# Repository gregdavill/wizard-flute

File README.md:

# Wizard Flute #

     ~ Current Status: Prototype boards ordered ~
     
     Note: This design was performed in KiCad nightly , you will need a Nightly build to open and edit these source files.

## What is it?

ESP32-S2 + LED Display

A Compact 4 digit 7-segment clock display with an ESP32-S2 control board.

It is powered off a USB-C connection on the side of the unit, and features 1 button.

This design will become a desk clock that sets it's time from your local WiFi using NTP.

## Licence
 * Hardware in this repository is licensed under CERN-OHL-P

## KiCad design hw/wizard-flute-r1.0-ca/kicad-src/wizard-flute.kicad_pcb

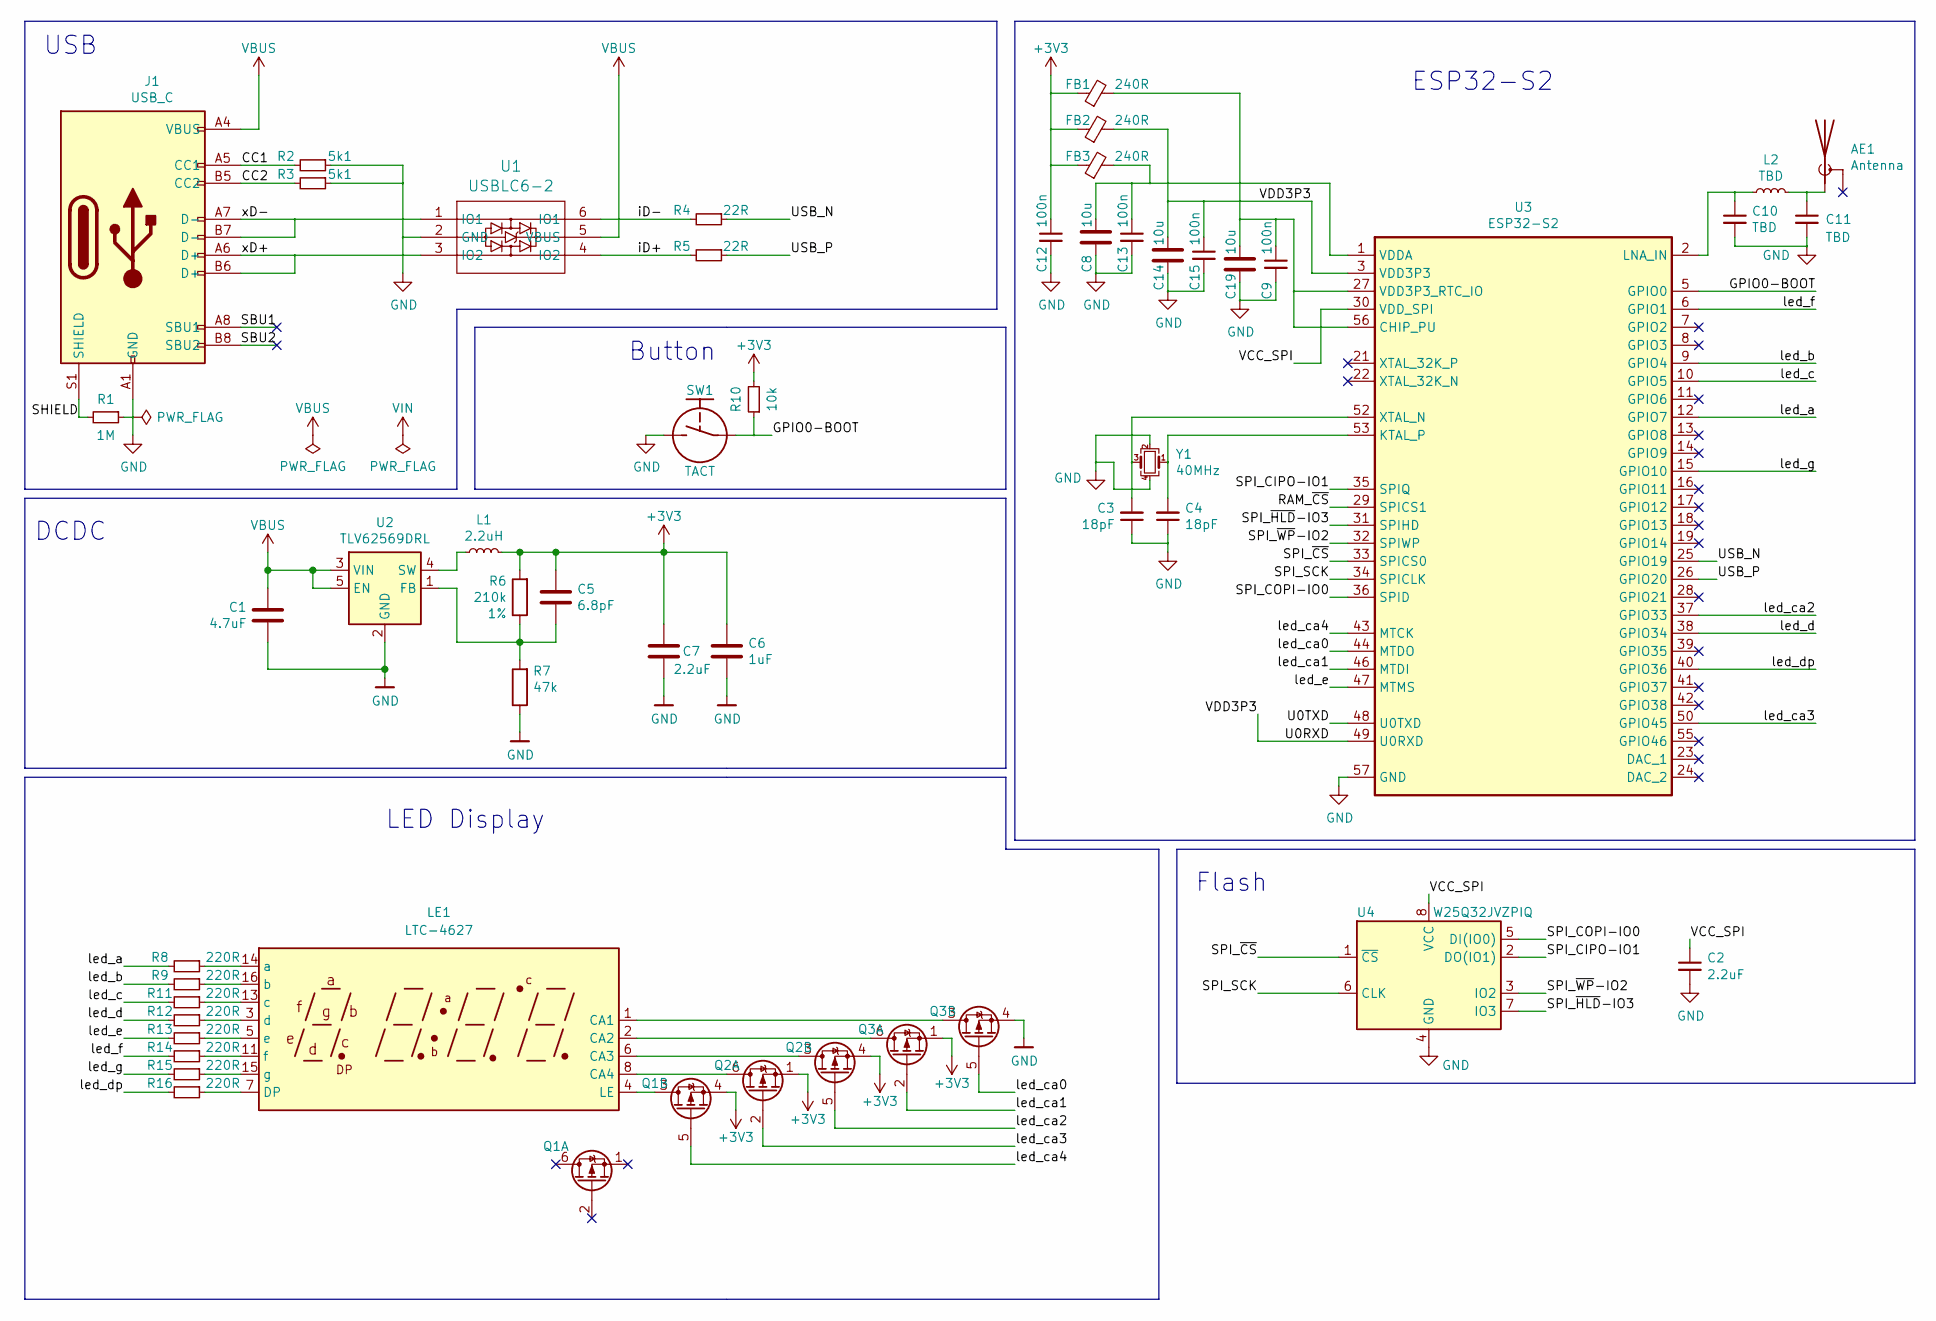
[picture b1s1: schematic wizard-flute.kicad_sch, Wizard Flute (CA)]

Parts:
AE1: Antenna; Ant_3216
C1: 4.7uF; C_0402_1005Metric
C2, C7: 2.2uF; C_0402_1005Metric
C3, C4: 18pF; C_0402_1005Metric
C5: 6.8pF; C_0402_1005Metric
C6: 1uF; C_0402_1005Metric
C8, C14, C19: 10u; C_0603_1608Metric
C9, C12, C13, C15: 100n; C_0402_1005Metric
C10, C11: TBD; C_0402_1005Metric
FB1, FB2, FB3: 240R; L_0402_1005Metric
J1: USB_C; USB_C_Receptacle_HRO_TYPE-C-31-M-12
L1: 2.2uH; L_0805_2012Metric
L2: TBD; L_0402_1005Metric
LE1: LTC-4627; kem-3942-ay
Q1, Q2, Q3: NTZD3152P; SOT-666
R1: 1M; R_0402_1005Metric
R2, R3: 5k1; R_0402_1005Metric
R4, R5: 22R; R_0402_1005Metric
R6: 210k; R_0402_1005Metric
R7: 47k; R_0402_1005Metric
R8, R9, R11, R12, R13, R14, R15, R16: 220R; R_0402_1005Metric
R10: 10k; R_0402_1005Metric
SW1: TACT; SW_SPST_3x4x2.5
U1: USBLC6-2; SOT-666
U2: TLV62569DRL; SOT-666
U3: ESP32-S2; QFN-56-1EP_7x7mm_P0.4mm_EP5.6x5.6mm
U4: W25Q32JVZPIQ; WSON-8-1EP_6x5mm_P1.27mm_EP3.4x4mm
Y1: 40MHz; Crystal_SMD_4Pin_2.0x1.6mm

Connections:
+3V3: C5.1, C6.1, C7.1, C12.1, FB1.1, FB2.1, FB3.1, L1.2, Q1.4 (S), Q2.1 (S), Q2.4 (S), Q3.1 (S), R6.2, R10.2
/CC1: J1.A5 (CC1), R2.2
/CC2: J1.B5 (CC2), R3.2
/GPIO0-BOOT: R10.1, SW1.1, U3.5 (GPIO0)
/RAM_~CS: U3.29 (SPICS1)
/SBU1: J1.A8 (SBU1)
/SBU2: J1.B8 (SBU2)
/SHIELD: J1.S1 (SHIELD), R1.2
/SPI_CIPO-IO1: U3.35 (SPIQ), U4.2 (DO(IO1))
/SPI_COPI-IO0: U3.36 (SPID), U4.5 (DI(IO0))
/SPI_SCK: U3.34 (SPICLK), U4.6 (CLK)
/SPI_~CS: U3.33 (SPICS0), U4.1 (~CS)
/SPI_~HLD~-IO3: U3.31 (SPIHD), U4.7 (IO3)
/SPI_~WP~-IO2: U3.32 (SPIWP), U4.3 (IO2)
/U0RXD: C14.1, C15.1, FB2.2, U3.3 (VDD3P3), U3.4 (VDD3P3), U3.49 (U0RXD)
/U0TXD: U3.48 (U0TXD)
/USB_N: R4.1, U3.25 (GPIO19)
/USB_P: R5.1, U3.26 (GPIO20)
/VCC_SPI: C2.1, U3.30 (VDD_SPI), U4.8 (VCC)
/iD+: R5.2, U1.4 (IO2)
/iD-: R4.2, U1.6 (IO1)
/led_a: R8.2, U3.12 (GPIO7)
/led_b: R9.2, U3.9 (GPIO4)
/led_c: R11.2, U3.10 (GPIO5)
/led_ca0: Q3.5 (G), U3.44 (MTDO)
/led_ca1: Q3.2 (G), U3.46 (MTDI)
/led_ca2: Q2.5 (G), U3.37 (GPIO33)
/led_ca3: Q2.2 (G), U3.50 (GPIO45)
/led_ca4: Q1.5 (G), U3.43 (MTCK)
/led_d: R12.2, U3.38 (GPIO34)
/led_dp: R16.2, U3.40 (GPIO36)
/led_e: R13.2, U3.47 (MTMS)
/led_f: R14.2, U3.6 (GPIO1)
/led_g: R15.2, U3.15 (GPIO10)
/xD+: J1.A6 (D+), J1.B6 (D+), U1.3 (IO2)
/xD-: J1.A7 (D-), J1.B7 (D-), U1.1 (IO1)
GND: C1.2, C2.2, C3.1, C4.1, C6.2, C7.2, C8.2, C9.2, C10.2, C11.2, C12.2, C13.2, C14.2, C15.2, C19.2, J1.A1 (GND), J1.A12 (GND), J1.B1 (GND), J1.B12 (GND), Q3.4 (S), R1.1, R2.1, R3.1, R7.1, SW1.2, U1.2 (GND), U2.2 (GND), U3.57 (GND), U4.4 (GND), Y1.2, Y1.4
unnamed: AE1.1 (A), C11.1, L2.2
unnamed: C3.2, U3.52 (XTAL_N), Y1.3
unnamed: C4.2, U3.53 (KTAL_P), Y1.1
unnamed: C5.2, R6.1, R7.2, U2.1 (FB)
unnamed: C10.1, L2.1, U3.2 (LNA_IN)
unnamed: C8.1, C13.1, FB3.2, U3.1 (VDDA), U3.51 (VDDA), U3.54 (VDDA)
unnamed: C9.1, C19.1, FB1.2, U3.20 (VDD3P3_RTC), U3.27 (VDD3P3_RTC_IO), U3.45 (VDD3P3_CPU), U3.56 (CHIP_PU)
unnamed: L1.1, U2.4 (SW)
unnamed: LE1.1 (CA1), Q3.3 (D)
unnamed: LE1.2 (CA2), Q3.6 (D)
unnamed: LE1.4 (LE), Q1.3 (D)
unnamed: LE1.6 (CA3), Q2.3 (D)
unnamed: LE1.8 (CA4), Q2.6 (D)
unnamed: LE1.14 (a), R8.1
unnamed: LE1.16 (b), R9.1
unnamed: LE1.13 (c), R11.1
unnamed: LE1.3 (d), R12.1
unnamed: LE1.5 (e), R13.1
unnamed: LE1.11 (f), R14.1
unnamed: LE1.15 (g), R15.1
unnamed: LE1.7 (DP), R16.1
VBUS: C1.1, J1.A4 (VBUS), J1.A9 (VBUS), J1.B4 (VBUS), J1.B9 (VBUS), U1.5 (VBUS), U2.3 (VIN), U2.5 (EN)

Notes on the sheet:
DCDC
USB
LED Display
Button
Flash
ESP32-S2

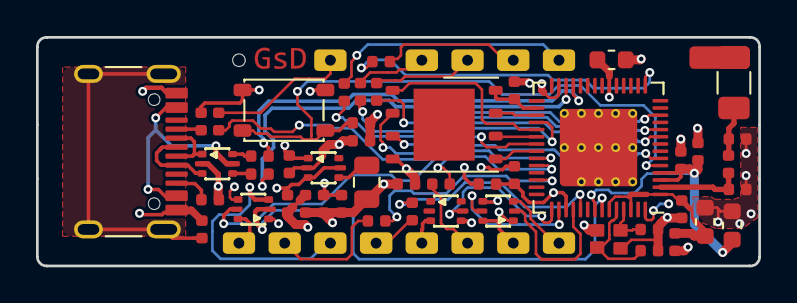
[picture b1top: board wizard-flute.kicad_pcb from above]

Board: 4 copper layers, 40.1 x 12.7 mm, 49 parts (1 on the bottom side), 55 nets.

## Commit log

2020-12-05 Fix spelling
2020-12-05 Add common-anode variant

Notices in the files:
hw/wizard-flute-r1.0-ca/kicad-src/wizard-flute.kicad_pcb:
© 2020 Greg Davill
License: CERN-OHL-P
